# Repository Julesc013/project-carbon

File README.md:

# Project Carbon

A family of retro-style computer designs (hardware code, simulators, and schematics) built around shared specifications so different implementations stay compatible.

## Overview

Project Carbon is a repository for designing and testing classic-style computers: it includes hardware design files, code that describes CPUs and systems, and simulators that let you run small programs without building physical hardware.

What makes it distinct is its **contract-first** approach: the architecture is defined as machine-readable specifications, and the project generates shared constants and documentation from those specs so every core, system, and test agrees on the same rules.

This reduces the chance that cores, tests, docs, and tools quietly diverge over time.

What it is **not**:
- A complete, end-user computer kit or a polished emulator distribution.
- A repository of copyrighted ROMs or operating system images (you must supply your own).
- A cycle-accurate reproduction of legacy buses and full peripheral ecosystems (many peripherals and timing models are explicitly deferred).

## Keypoints

- Frozen v1.0 architecture contracts in `hdl/spec/*.yaml` with generated SystemVerilog/C constants.
- Compatibility tier ladders and a single mode-switching contract (`MODEUP`/`RETMD`).
- Shared HDL interfaces (fabric/CSR/IRQ/debug/accelerator) plus contract tests.
- SystemVerilog cores: Z85, Z90, Z380, Z480 (P7 subset) and Am9513/Am9514/Am9515.
- x86/x87 lineage is explicitly deferred in v1.0 (see `docs/DEFERRED.md`).
- Integrated system simulation tops and regression runner targeting Icarus Verilog.
- `carbon-sim` C++ simulator for CP/M 2.2 and RomWBW-style platforms (ROMs not included).
- KiCad hardware: a Carbon_Z80 project plus a KiCad 9 schematic skeleton generator.

## Architecture

### Layering (source-of-truth → generated → implementations)

- **Docs & contracts**
  - `docs/ARCHITECTURE_OVERVIEW.md`: human overview of the v1.0 contract freeze.
  - `hdl/spec/*.yaml`: machine-readable source of truth.
  - `hdl/tools/gen_specs.py` → generates `hdl/gen/*` and renders `docs/ARCH_CONTRACTS.md`.
- **HDL cores (CPU/accelerators)**
  - `hdl/cores/*`: CPU families and accelerators (RTL + testbenches + per-core docs).
- **HDL systems (integrations)**
  - `hdl/systems/*`: integrated "tops" (core + ROM/RAM + memory-mapped I/O + wiring) with smoke tests and memory maps.
- **HDL simulation & verification**
  - `hdl/sim/*`: Makefile-based smoke/contract/system tests (Icarus Verilog), driven by `hdl/sim/tests/regress.yaml`.
- **Host-level simulator(s)**
  - `source/sim/carbon_sim`: `carbon-sim` (C++17) with CP/M 2.2, RomWBW, and CarbonZ platform models; optional Verilator backend is scaffolding.
- **OS/software/firmware (repository content)**
  - `source/`: currently includes `carbon-sim`, a bundled Small Computer Workshop tool under `source/SCM/`, and placeholder directories (e.g., `source/JC-BIOS`, `source/JC-DOS`).
- **Schematics**
  - `schem/Carbon_Z80`: a KiCad project with exported PDFs/PNGs/SVGs under `schem/Carbon_Z80/export/`.
  - `schem/kicad9`: generator-owned schematic skeletons (`generated/`) plus hand-edited space (`manual/`) driven by mapping specs (`spec/`).

### Boot models (summary)

- **Carbon native boot**: ROM discovery → BDT/CAPSET → BIOS services → OS handoff.
- **Z80 boot** (RC2014/S-100 and similar): board pack or ROMWBW hooks; see `docs/boot_z80.md`.
- **PC BIOS boot**: PAL hooks with BIOS services; see `docs/boot_pcbios.md`.

### Design philosophy (as implemented in v1)

- **Determinism & reproducibility**: generators are deterministic; CI verifies generated outputs are committed.
- **Explicit contracts**: shared enums/bitfields/opcode pages/queue formats live in specs, not ad-hoc RTL.
- **Portability-minded tooling**: scripts exist for POSIX shell and PowerShell; generators avoid third-party dependencies.
- **Long-term maintainability**: clean module boundaries (notably the Z480 scaffold) so implementations can evolve behind stable interfaces.

## Platforms

Hardware targets (v1 focus):
- **Carbon native SoCs** (Z85/Z90/Z380/Z480 system tops).
- **Z80-class boards** via board packs (RC2014, S-100).
- **PC compatibles** via PAL BIOS hooks (UEFI PAL is a stub in v1).

Primary (actively used by the repo and CI):
- **HDL regression**: Icarus Verilog (`iverilog`/`vvp`) + `make` via `hdl/sim/`.
- **Spec/code generation**: Python via `scripts/gen_arch.*`.

Secondary / experimental:
- **`carbon-sim` desktop simulator**: CMake build (`source/sim/carbon_sim`); optional Verilator backend is preview scaffolding.
- **KiCad schematics**: Carbon_Z80 KiCad project and KiCad 9 generated skeletons under `schem/kicad9/generated/`.

Compatibility overview (guest focus):
- **CP/M** (2.x/3.x) and RomWBW-style guests are target environments.
- **DOS** real-mode guests are hosted via EE providers.
- **GEM** and **Windows** compatibility notes live in `docs/compat_gem.md` and `docs/compat_windows.md`.

## Audience

This project is for:
- RTL/hardware engineers exploring CPU, accelerator, and system integration patterns with explicit contracts.
- Retrocomputing hobbyists who want a testable platform (simulation + schematics) for “small computer” designs.
- Contributors who prefer deterministic generators and contract tests over hand-maintained duplicated constants.

Example use cases:
- Implement a new core or accelerator that conforms to the v1 contract layer.
- Run contract/system smoke tests to validate integration plumbing.
- Use `carbon-sim` to bring up ROM-based environments you supply (e.g., CP/M or RomWBW variants).

Not a fit if you need:
- Turn-key ROMs/OS images or full software distributions.
- Full instruction/peripheral coverage and cycle-accurate platform timing (see deferred lists and per-core docs).

## Constraints

- **Contracts are the source of truth**: `hdl/spec/*.yaml` drives generated headers/packages and the rendered contract reference.
- **Generated outputs are treated as artifacts**: `hdl/gen/*` and `docs/ARCH_CONTRACTS.md` are generated and committed (verified in CI).
- **Minimal dependency stance**: key tooling is dependency-light (e.g., a deterministic, stdlib-only spec generator; a simple regression manifest; JSON-in-YAML KiCad mapping specs).
- **Compatibility and gating are explicit**: tier ladders, `MODEUP`/`RETMD`, and strict-mode extension gating are architectural concepts, not local hacks.
- **Generated vs hand-edited separation**: `schem/kicad9/generated/` is safe to overwrite; `schem/kicad9/manual/` is not.

## Structure

- `docs/`: architecture/contracts docs plus legacy design notes, manuals, datasheets, and images.
- `hdl/`: HDL contract layer and implementations.
  - `hdl/spec/`: v1.0 specs (source of truth).
  - `hdl/gen/`: generated constants (committed; do not hand-edit).
  - `hdl/common/`: shared interfaces/utilities.
  - `hdl/cores/`: CPU/accelerator RTL + TBs.
  - `hdl/systems/`: integrated system tops + TBs.
  - `hdl/sim/`: regression harness and tests.
- `schem/`: KiCad projects and schematic generation.
  - `schem/Model_150/`: board-level KiCad project + exports.
  - `schem/kicad9/`: generated/manual schematic trees + mapping specs.
- `source/`: software and simulator sources (notably `source/sim/carbon_sim`).
- `scripts/`: wrappers for regenerating specs, running HDL regressions, and regenerating KiCad skeletons.
- `tools/`: utilities (`tools/kicadgen` and `tools/mk_disk.py`).

## Documentation

- Documentation index: `docs/README.md`
- Architecture overview and layering: `docs/ARCHITECTURE.md`
- Hardware architecture: `docs/HARDWARE_ARCHITECTURE.md`
- Firmware architecture: `docs/FIRMWARE_ARCHITECTURE.md`
- OS architecture: `docs/OS_ARCHITECTURE.md`
- PAL and EE contract indexes: `docs/PAL.md` and `docs/EE.md`
- Contracts, determinism, and style: `docs/CONTRACTS.md`, `docs/DEPENDENCIES.md`,
  `docs/DETERMINISM.md`, `docs/STYLE.md`
- Frozen contract reference (generated): `docs/ARCH_CONTRACTS.md`
- Spec entry points: `docs/SPEC_*.md`
- Compatibility ladders (CPU/FPU tiers): `docs/COMPAT_LADDERS.md`
- System memory map index: `docs/platform/SYSTEM_MEMORY_MAPS.md`
- CPU core docs:
  - `hdl/cores/Z85/docs/Z85_v1.md`
  - `hdl/cores/Z90/docs/Z90_v1.md`
  - `hdl/cores/Z380/docs/Z380.md`
  - `hdl/cores/Z480/docs/Z480.md`
- FPU tier docs:
  - `docs/fpu/Am9513.md`
  - `docs/fpu/Am9514.md`
  - `docs/fpu/Am9515.md`
- Verification flow and regression philosophy: `docs/VERIFICATION.md`
- HDL contract layer README: `hdl/README.md`
- v1.0 release contents: `docs/RELEASE_v1.md`
- Deferred/non-goals list (v1.0): `docs/DEFERRED.md`
- HDL simulation prerequisites/usage: `hdl/sim/README.md`
- System memory maps & smoke tests (examples):
  - `hdl/systems/CarbonZ80/docs/MEMORY_MAP.md`
  - `hdl/systems/CarbonX96/docs/MEMORY_MAP.md`
- `carbon-sim` usage and platform maps:
  - `source/sim/carbon_sim/docs/USAGE.md`
  - `source/sim/carbon_sim/docs/PLATFORMS.md`
  - ROM policy: `source/sim/carbon_sim/roms/README.md`
- KiCad 9 generated/manual workflow: `schem/kicad9/docs/USAGE.md`
- Carbon_Z80 schematic/PCB exports: `schem/Carbon_Z80/export/Carbon_Z80_150_sch_rev1.pdf`
- Release notes: `CHANGELOG.md`

## Build

- HDL (generate + run regressions): see `hdl/sim/README.md` and `docs/RELEASE_v1.md`.
- `carbon-sim` (build/run): see `source/sim/carbon_sim/docs/USAGE.md`.
- KiCad skeleton regeneration: see `schem/kicad9/docs/USAGE.md`.

## Status

- Repository version: **v1.0.0** (`VERSION`).
- The **contract/spec layer is frozen for v1.0** and the generator outputs are CI-checked for reproducibility.
- Several cores and systems are intentionally **subset implementations** (e.g., partial legacy ISA coverage, minimal peripherals); see `docs/DEFERRED.md` and the per-core docs under `hdl/cores/*/docs/`.
- x86/x87 lineage and CarbonX* system validation are deferred for v1.0.
- The primary “known-good” workflows in v1.0 are spec generation and HDL regression in CI; additional platforms (e.g., `carbon-sim` backends) evolve separately.

## License

License: just behave yourselves.

## Contributing

This repository includes CI and regression tooling under `.github/` and `scripts/`. If you contribute changes, keep generated outputs in sync and include enough context in your PR/commit to review the contract impact.

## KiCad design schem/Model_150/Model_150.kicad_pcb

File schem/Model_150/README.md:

Model: 150
Family: Carbon
Processor: Z80

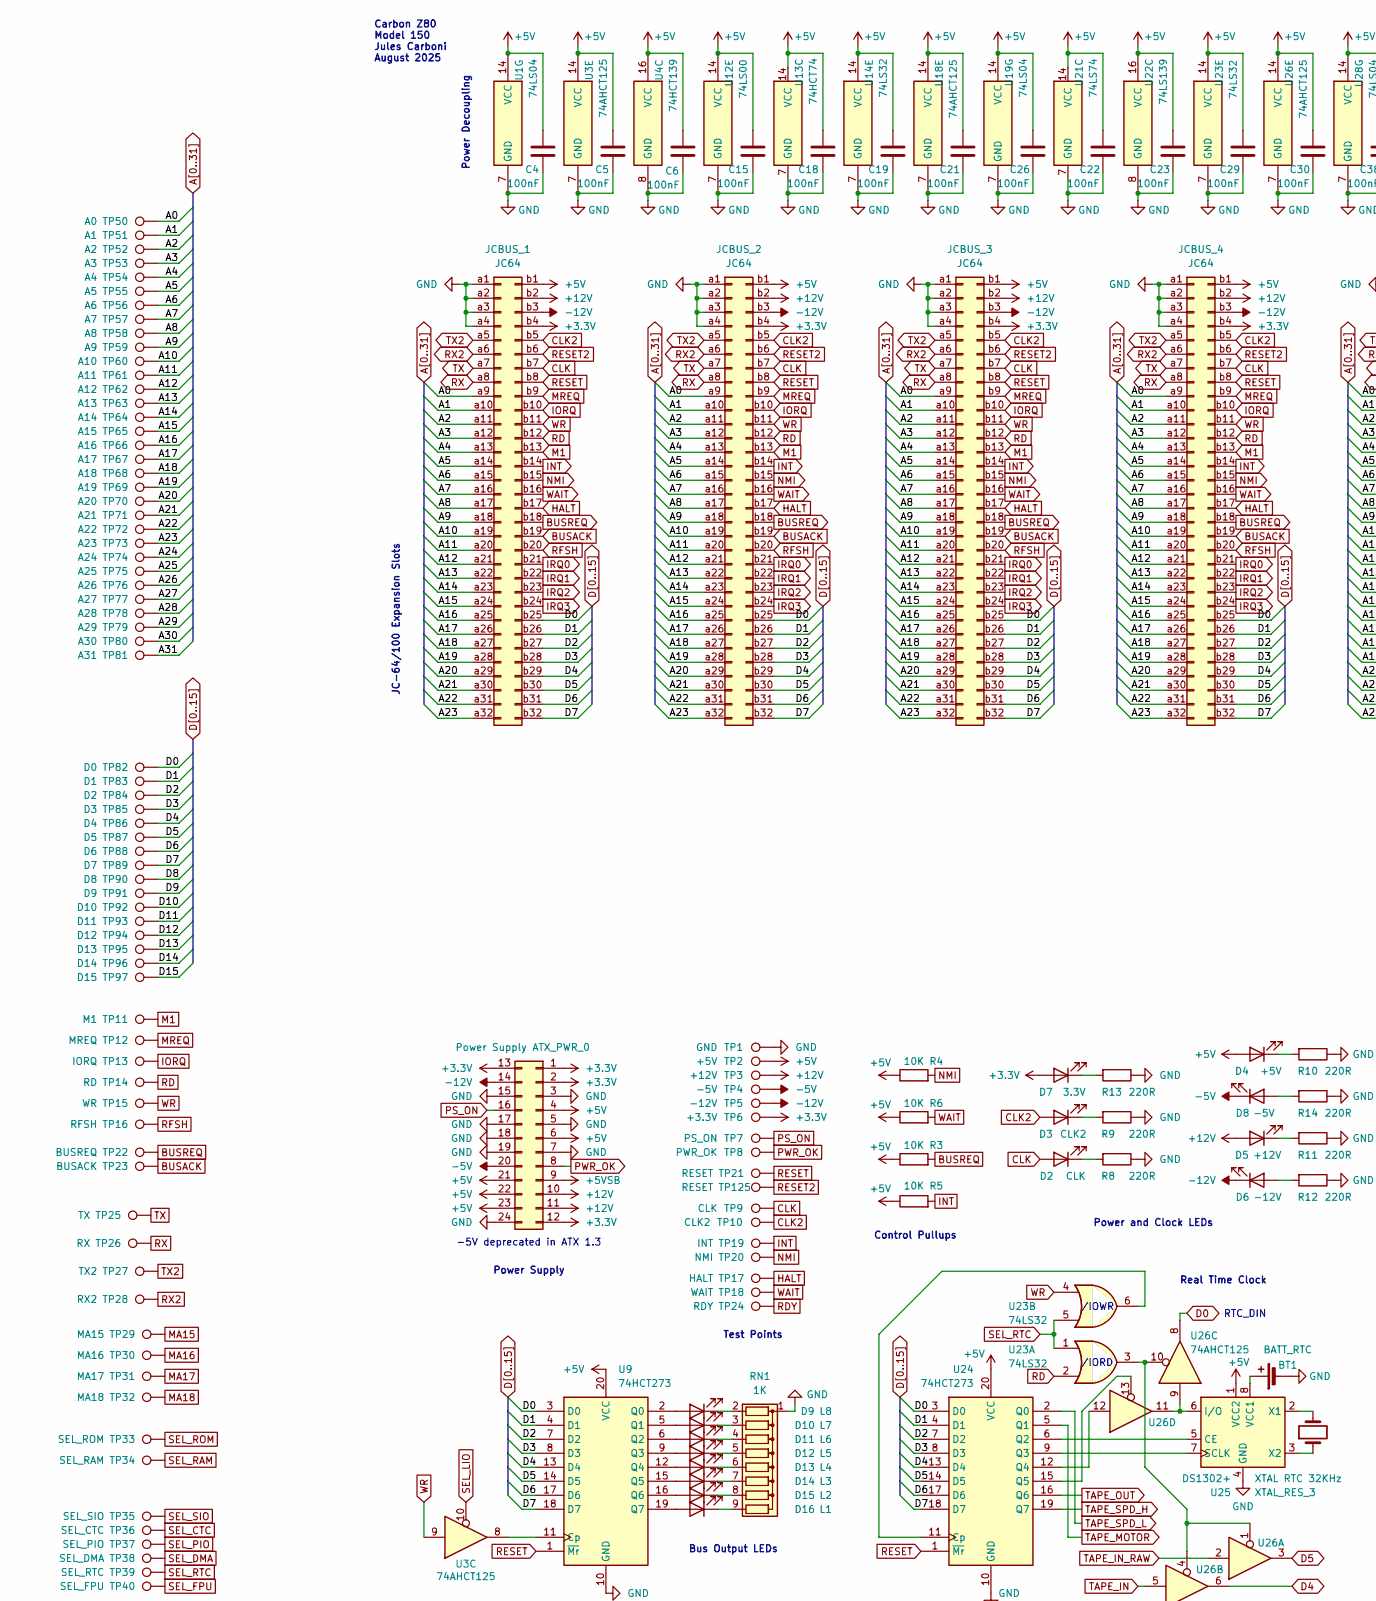
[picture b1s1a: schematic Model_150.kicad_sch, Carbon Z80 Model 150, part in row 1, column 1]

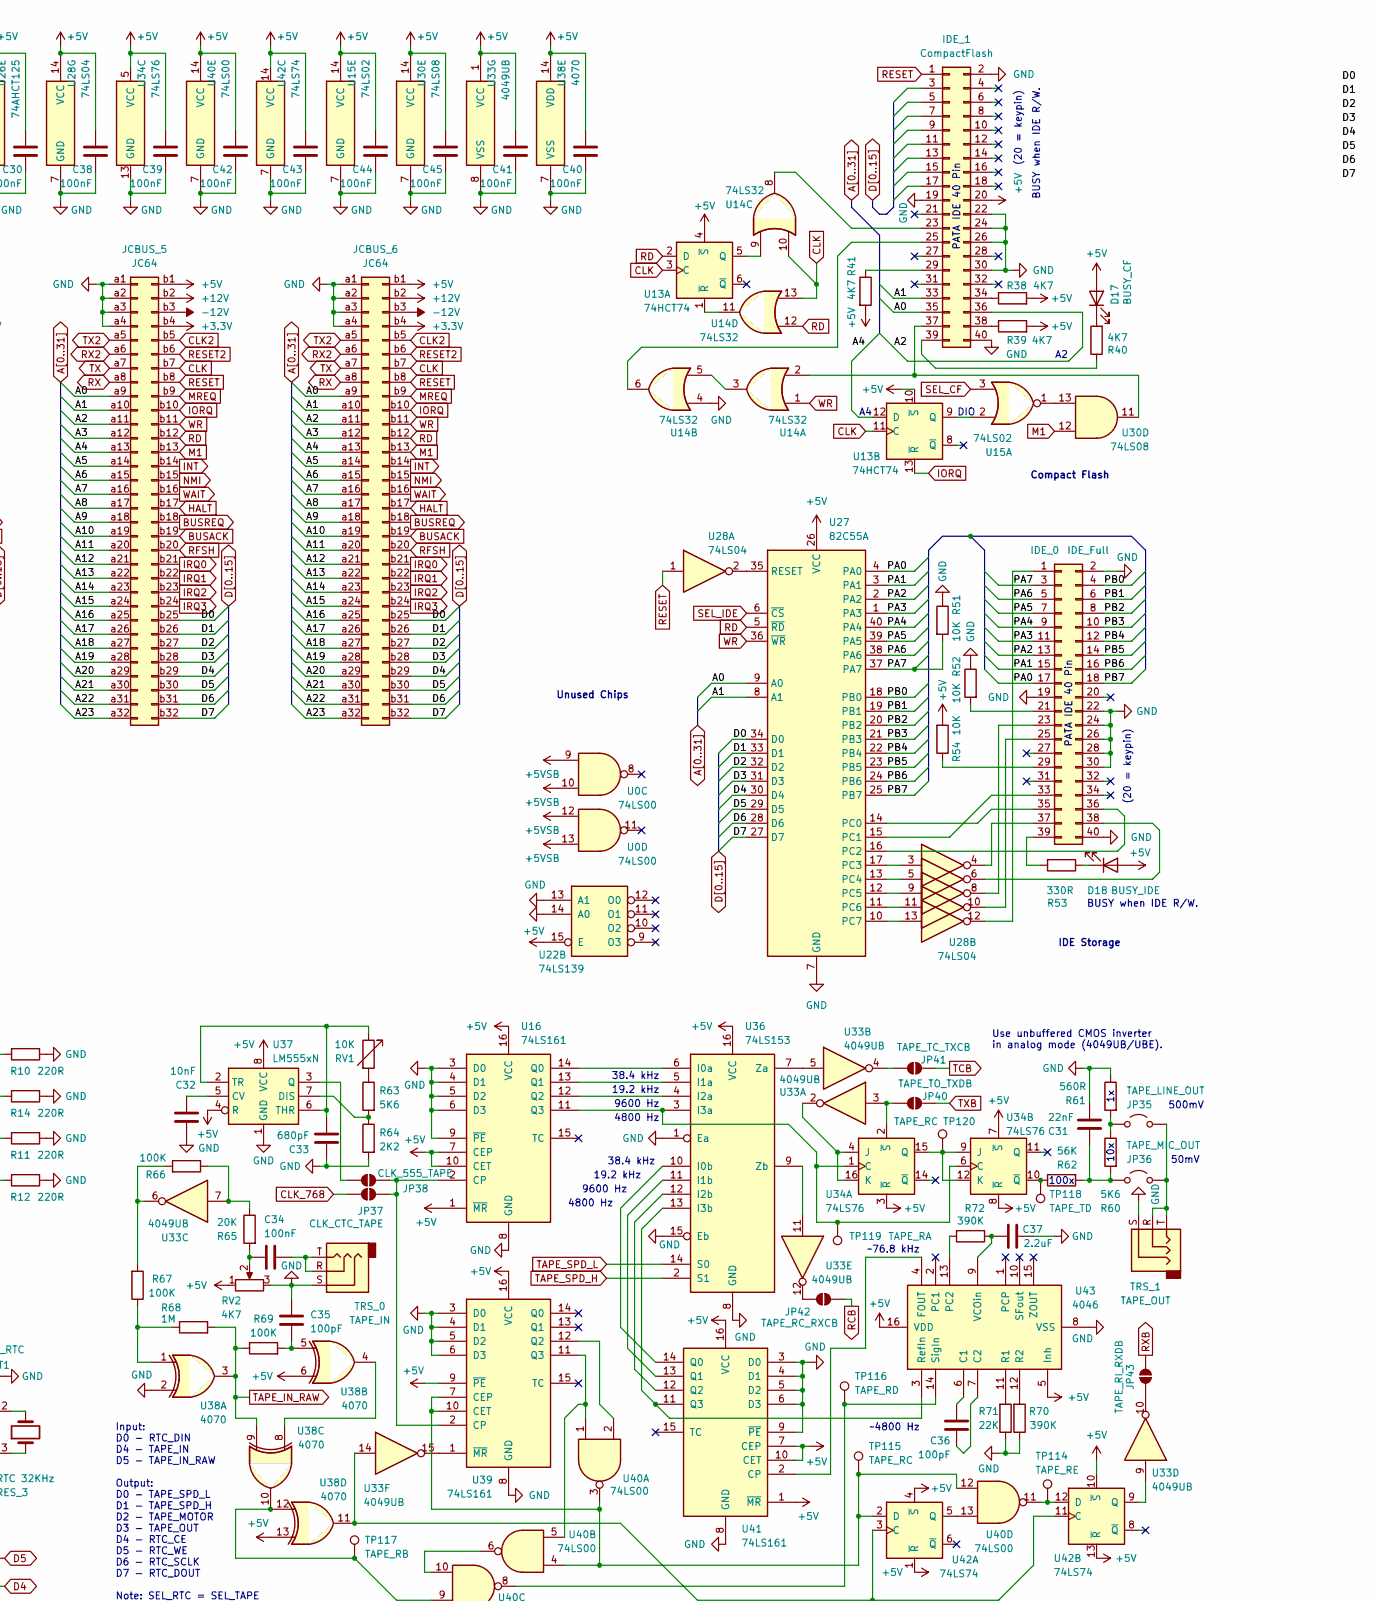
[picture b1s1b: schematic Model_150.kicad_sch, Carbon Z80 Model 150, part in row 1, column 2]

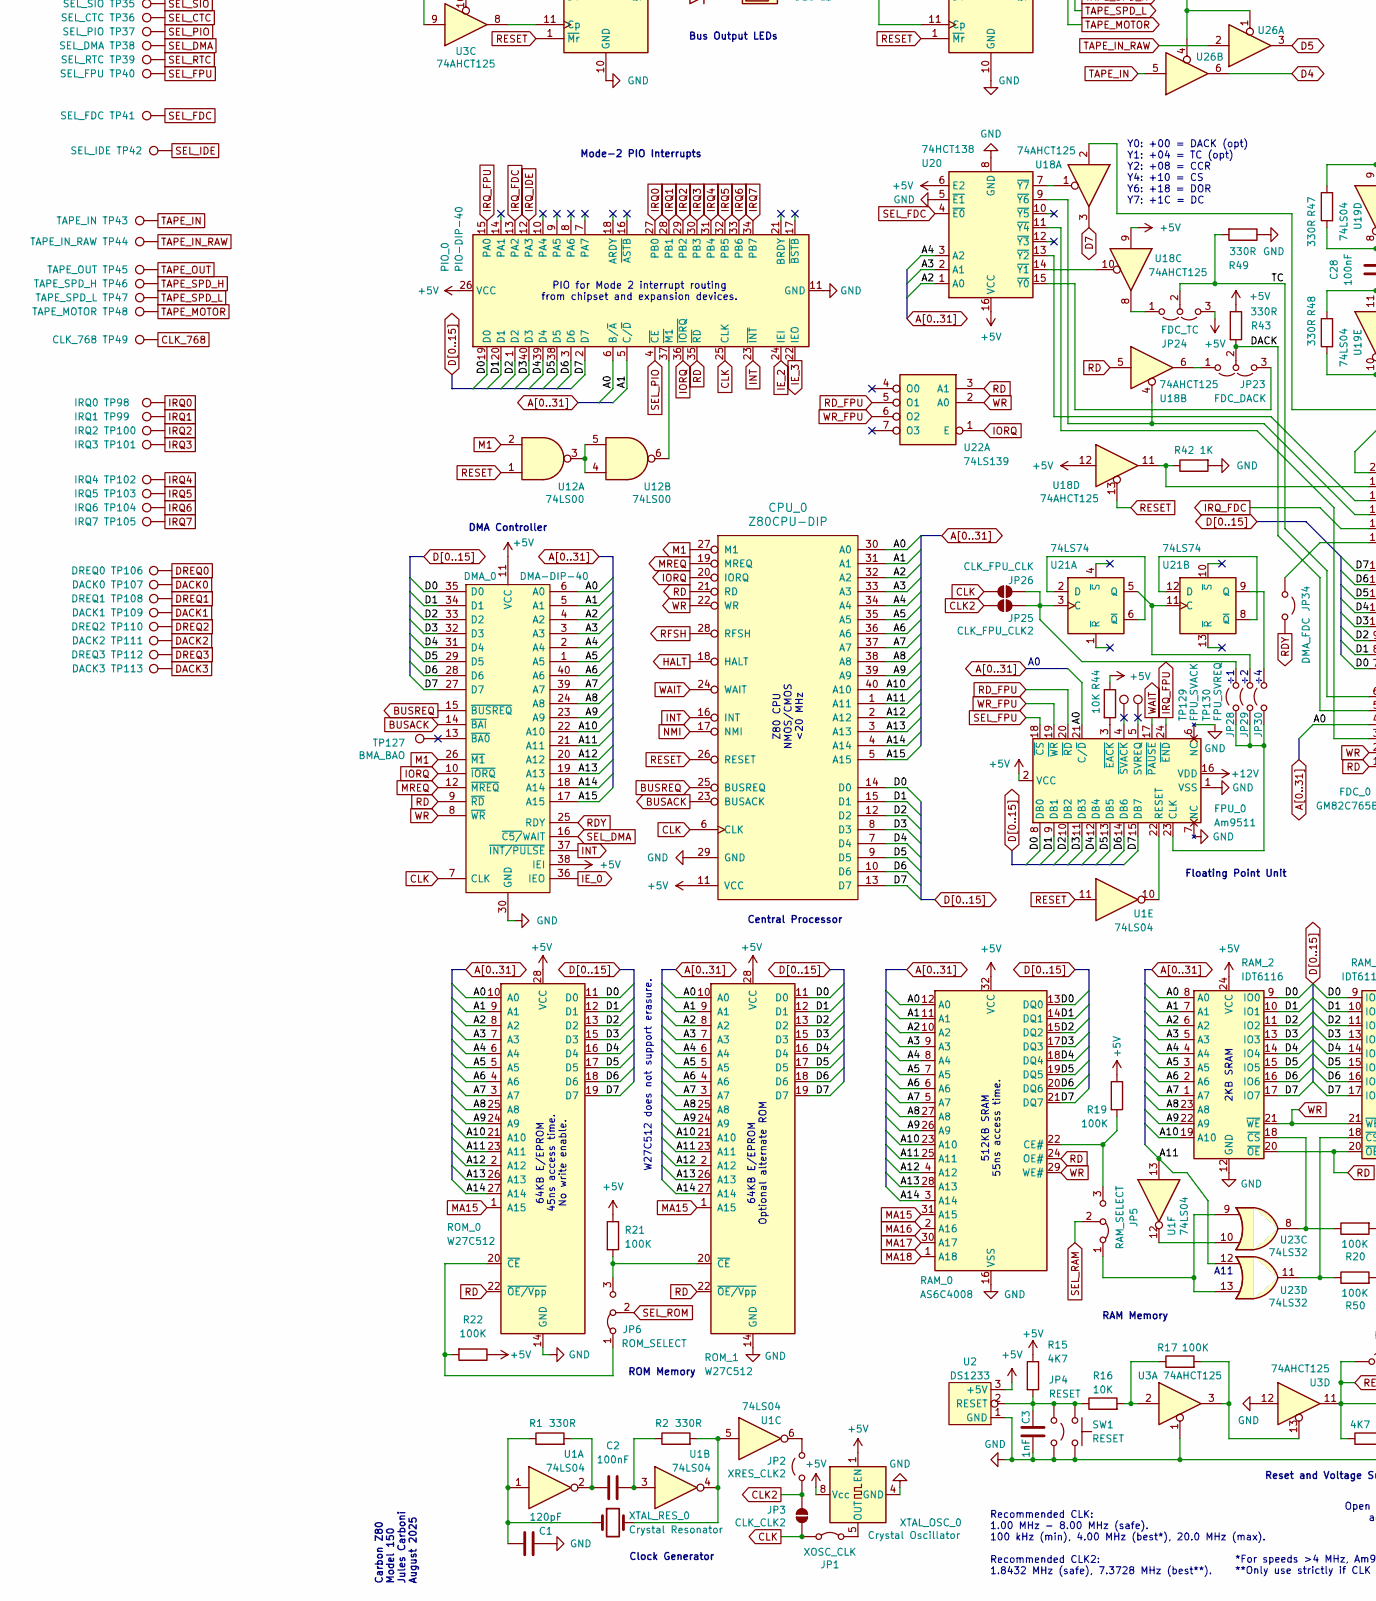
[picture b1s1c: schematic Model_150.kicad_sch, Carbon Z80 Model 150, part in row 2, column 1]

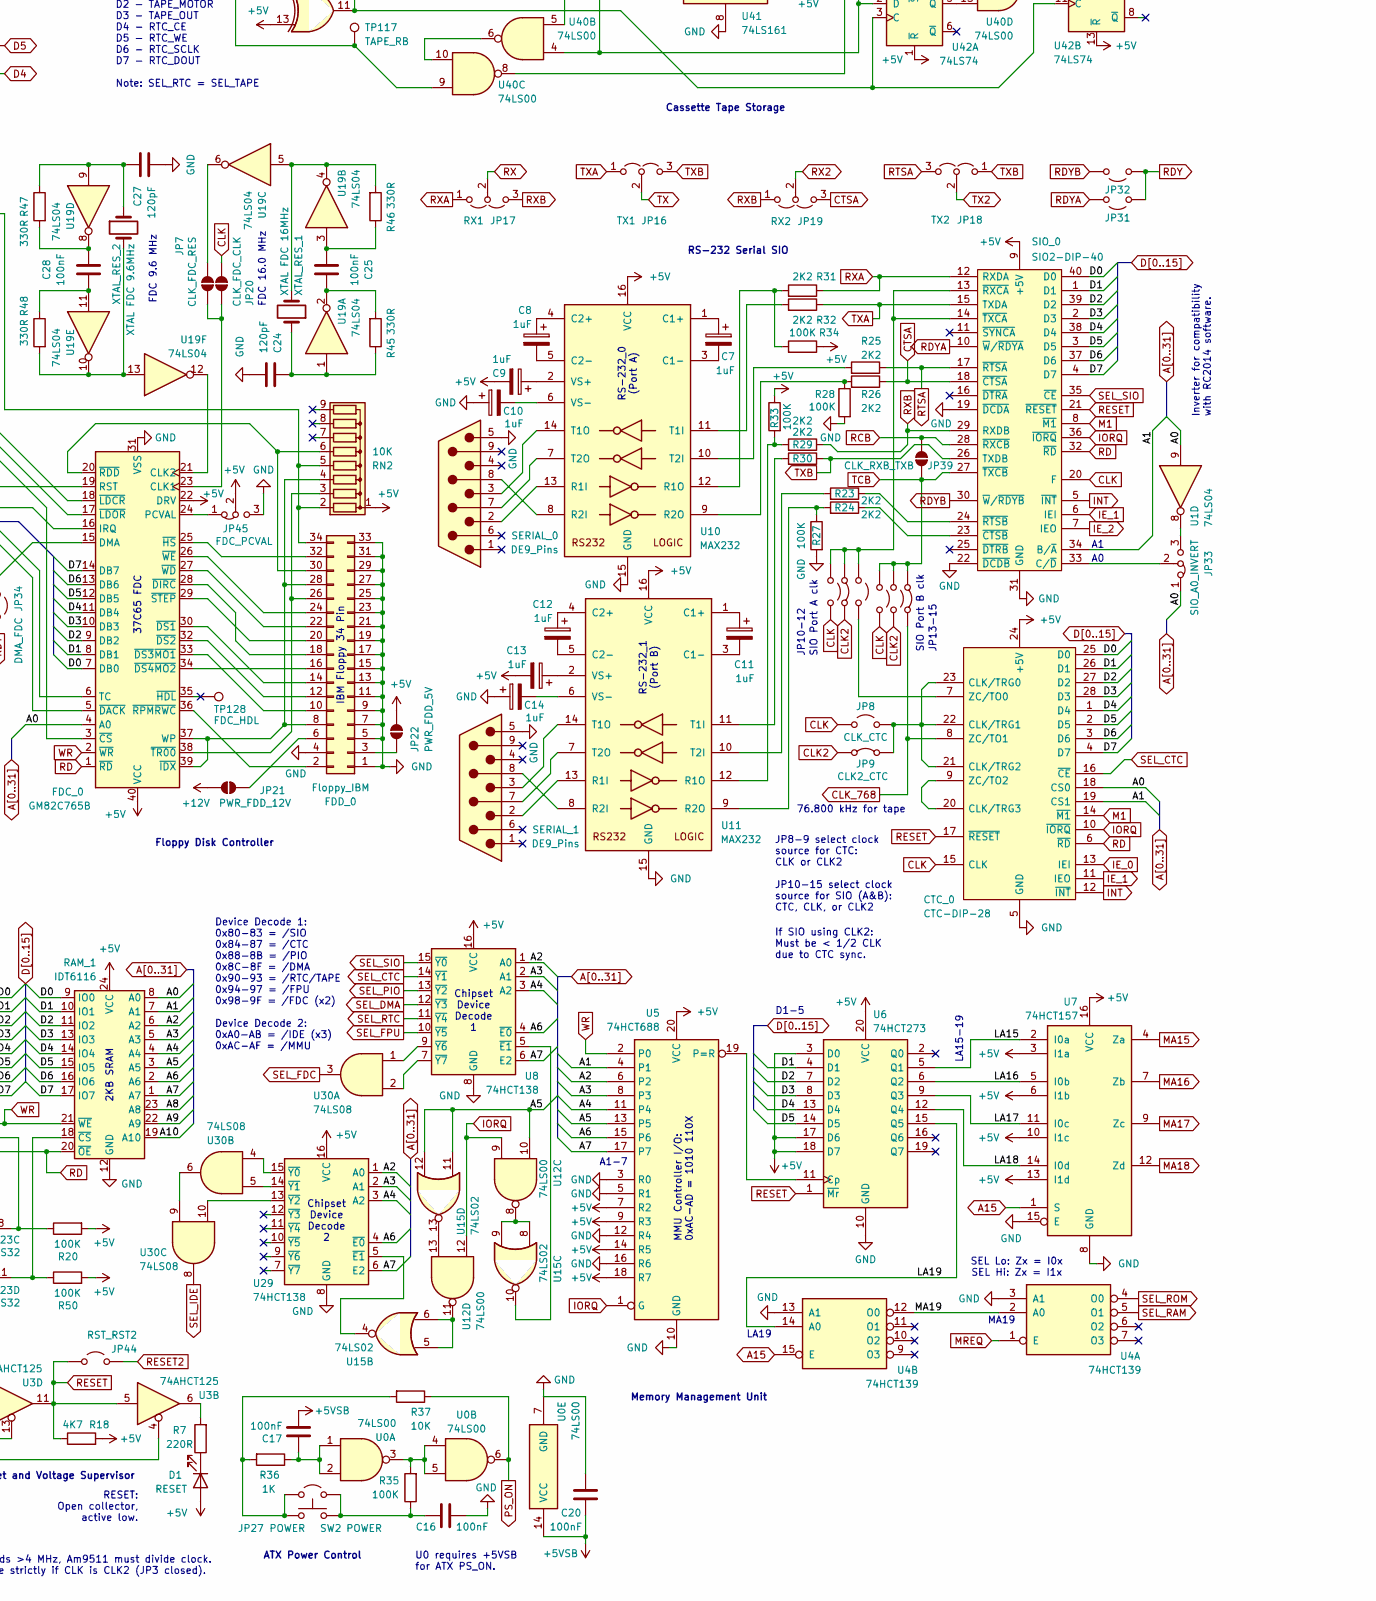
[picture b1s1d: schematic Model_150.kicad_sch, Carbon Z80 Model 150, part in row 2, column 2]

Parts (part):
ATX_PWR_0: Power Supply; Molex_Mini-Fit_Jr_5566-24A_2x12_P4.20mm_Vertical
BT1: BATT_RTC; BatteryHolder_MYOUNG_BS-07-A1BJ001_CR2032
C1, C24, C27: 120pF; C_Disc_D3.4mm_W2.1mm_P2.50mm
C2, C4, C5, C6, C15, C16, C17, C18, C19, C20, C21, C22, C23, C25, C26, C28, C29, C30, C34, C38, C39, C40, C41, C42, C43, C44, C45: 100nF; C_Disc_D5.0mm_W2.5mm_P2.50mm
C3: 1nF; C_Disc_D5.0mm_W2.5mm_P2.50mm
C7, C8, C9, C10, C11, C12, C13, C14: 1uF; CP_Radial_D4.0mm_P2.00mm
C31: 22nF; C_Rect_L7.0mm_W3.5mm_P5.00mm
C32: 10nF
C33: 680pF
C35, C36: 100pF; C_Disc_D3.4mm_W2.1mm_P2.50mm
C37: 2.2uF; C_Disc_D6.0mm_W2.5mm_P5.00mm
CPU_0: Z80CPU-DIP; DIP-40_W15.24mm_Socket
CTC_0: CTC-DIP-28; DIP-28_W15.24mm_LongPads; Manufacturer_Part_Number Z84C3010PEG; Mouser Part Number 692-Z84C3010PEG
D1: RESET; LED_D5.0mm
D2: CLK; LED_D5.0mm
D3: CLK2; LED_D5.0mm
D4: +5V; LED_D5.0mm
D5: +12V; LED_D5.0mm
D6: -12V; LED_D5.0mm
D7: 3.3V; LED_D5.0mm
D8: -5V; LED_D5.0mm
D9: L8; LED_D5.0mm
D10: L7; LED_D5.0mm
D11: L6; LED_D5.0mm
D12: L5; LED_D5.0mm
D13: L4; LED_D5.0mm
D14: L3; LED_D5.0mm
D15: L2; LED_D5.0mm
D16: L1; LED_D5.0mm
D17: BUSY_CF; LED_D5.0mm
D18: BUSY_IDE; LED_D5.0mm
DMA_0: DMA-DIP-40; DIP-40_W15.24mm_Socket; Manufacturer_Part_Number Z84C4206PEG; Mouser Part Number 692-Z84C4206PEG
FDC_0: GM82C765B; DIP-40_W15.24mm_Socket
FDD_0: Floppy_IBM; IDC-Header_2x17_P2.54mm_Vertical
FPU_0: Am9511; DIP-24_W15.24mm
IDE_0: IDE_Full; IDC-Header_2x20_P2.54mm_Vertical
IDE_1: CompactFlash; IDC-Header_2x20_P2.54mm_Vertical
JCBUS_1, JCBUS_2, JCBUS_3, JCBUS_4, JCBUS_5, JCBUS_6: JC64; JC64_Bus_8b
JP1: XOSC_CLK; PinHeader_1x02_P2.54mm_Vertical
JP2: XRES_CLK2; PinHeader_1x02_P2.54mm_Vertical
JP3: CLK_CLK2
JP4: RESET; PinHeader_1x02_P2.54mm_Vertical
JP5: RAM_SELECT; PinHeader_1x03_P2.54mm_Vertical
JP6: ROM_SELECT; PinHeader_1x03_P2.54mm_Vertical
JP7: CLK_FDC_RES
JP8: CLK_CTC; PinHeader_1x02_P2.54mm_Vertical
JP9: CLK2_CTC
JP10: CLK_SIOA; PinHeader_1x02_P2.54mm_Vertical
JP11: CLK2_SIOA
JP12: CTC_SIOA; PinHeader_1x02_P2.54mm_Vertical
JP13: CLK_SIOB; PinHeader_1x02_P2.54mm_Vertical
JP14: CLK2_SIOB; PinHeader_1x02_P2.54mm_Vertical
JP15: CTC_SIOB
JP16: TX1; PinHeader_1x03_P2.54mm_Vertical
JP17: RX1; PinHeader_1x03_P2.54mm_Vertical
JP18: TX2; PinHeader_1x03_P2.54mm_Vertical
JP19: RX2; PinHeader_1x03_P2.54mm_Vertical
JP20: CLK_FDC_CLK
JP21: PWR_FDD_12V
JP22: PWR_FDD_5V
JP23: FDC_DACK; PinHeader_1x03_P2.54mm_Vertical
JP24: FDC_TC; PinHeader_1x03_P2.54mm_Vertical
JP25: CLK_FPU_CLK2
JP26: CLK_FPU_CLK
JP27: POWER; PinHeader_1x02_P2.54mm_Vertical
JP28: FPU_CLKd1; PinHeader_1x02_P2.54mm_Vertical
JP29: FPU_CLKd2; PinHeader_1x02_P2.54mm_Vertical
JP30: FPU_CLKd4; PinHeader_1x02_P2.54mm_Vertical
JP31: DMA_RDYA; PinHeader_1x02_P2.54mm_Vertical
JP32: DMA_RDYB; PinHeader_1x02_P2.54mm_Vertical
JP33: SIO_A0_INVERT; PinHeader_1x03_P2.54mm_Vertical
JP34: DMA_FDC; PinHeader_1x02_P2.54mm_Vertical
JP35: TAPE_LINE_OUT
JP36: TAPE_MIC_OUT
JP37: CLK_CTC_TAPE
JP38: CLK_555_TAPE
JP39: CLK_RXB_TXB
JP40: TAPE_TO_TXDB
JP41: TAPE_TC_TXCB
JP42: TAPE_RC_RXCB
JP43: TAPE_RI_RXDB
JP44: RST_RST2; PinHeader_1x02_P2.54mm_Vertical
JP45: FDC_PCVAL; PinHeader_1x03_P2.54mm_Vertical
PIO_0: PIO-DIP-40; DIP-40_W15.24mm_Socket
R1, R2, R43, R45, R46, R47, R48, R49: 330R
R3, R4, R5, R6, R16, R37, R44, R52, R54: 10K; R_Axial_DIN0207_L6.3mm_D2.5mm_P10.16mm_Horizontal
R7, R8, R9, R10, R11, R12, R13, R14: 220R; R_Axial_DIN0207_L6.3mm_D2.5mm_P10.16mm_Horizontal
R15, R18, R38, R39, R40, R41: 4K7; R_Axial_DIN0207_L6.3mm_D2.5mm_P10.16mm_Horizontal
R17, R19, R20, R21, R22, R27, R28, R33, R34, R35, R50, R66, R67, R69: 100K; R_Axial_DIN0207_L6.3mm_D2.5mm_P10.16mm_Horizontal
R23, R24, R25, R26, R29, R30, R31, R32, R64: 2K2; R_Axial_DIN0207_L6.3mm_D2.5mm_P10.16mm_Horizontal
R36, R42: 1K; R_Axial_DIN0207_L6.3mm_D2.5mm_P10.16mm_Horizontal
R51: 10K
R53: 330R; R_Axial_DIN0207_L6.3mm_D2.5mm_P10.16mm_Horizontal
R60, R63: 5K6; R_Axial_DIN0207_L6.3mm_D2.5mm_P10.16mm_Horizontal
R61: 560R; R_Axial_DIN0207_L6.3mm_D2.5mm_P10.16mm_Horizontal
R62: 56K; R_Axial_DIN0207_L6.3mm_D2.5mm_P10.16mm_Horizontal
R65: 20K; R_Axial_DIN0207_L6.3mm_D2.5mm_P10.16mm_Horizontal
R68: 1M; R_Axial_DIN0207_L6.3mm_D2.5mm_P10.16mm_Horizontal
R70, R72: 390K; R_Axial_DIN0207_L6.3mm_D2.5mm_P10.16mm_Horizontal
R71: 22K; R_Axial_DIN0207_L6.3mm_D2.5mm_P10.16mm_Horizontal
RAM_0: AS6C4008; DIP-32_W15.24mm_Socket
RAM_1, RAM_2: IDT6116; DIP-24_W15.24mm_Socket
RN1: 1K; R_Array_SIP9
RN2: 10K; R_Array_SIP9
ROM_0, ROM_1: W27C512; DIP-28_W15.24mm_Socket
RV1: 10K
RV2: 4K7
SERIAL_0, SERIAL_1: DE9_Pins; DSUB-9_Pins_Horizontal_P2.77x2.84mm_EdgePinOffset7.70mm_Hou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
SIO_0: SIO2-DIP-40; DIP-40_W15.24mm_Socket; Manufacturer_Part_Number Z84C4206PEG; Mouser Part Number 692-Z84C4206PEG
SW1: RESET; SW_PUSH_6mm
SW2: POWER; SW_PUSH_6mm
TP1: GND; TestPoint_THTPad_1.5x1.5mm_Drill0.7mm
TP2: +5V; TestPoint_THTPad_1.5x1.5mm_Drill0.7mm
TP3: +12V; TestPoint_THTPad_1.5x1.5mm_Drill0.7mm
TP4: -5V; TestPoint_THTPad_1.5x1.5mm_Drill0.7mm
TP5: -12V; TestPoint_THTPad_1.5x1.5mm_Drill0.7mm
TP6: +3.3V; TestPoint_THTPad_1.5x1.5mm_Drill0.7mm
TP7: PS_ON; TestPoint_THTPad_1.5x1.5mm_Drill0.7mm
TP8: PWR_OK; TestPoint_THTPad_1.5x1.5mm_Drill0.7mm
TP9: CLK; TestPoint_THTPad_1.5x1.5mm_Drill0.7mm
TP10: CLK2; TestPoint_THTPad_1.5x1.5mm_Drill0.7mm
TP11: M1; TestPoint_THTPad_1.5x1.5mm_Drill0.7mm
TP12: MREQ; TestPoint_THTPad_1.5x1.5mm_Drill0.7mm
TP13: IORQ; TestPoint_THTPad_1.5x1.5mm_Drill0.7mm
TP14: RD; TestPoint_THTPad_1.5x1.5mm_Drill0.7mm
TP15: WR; TestPoint_THTPad_1.5x1.5mm_Drill0.7mm
TP16: RFSH; TestPoint_THTPad_1.5x1.5mm_Drill0.7mm
TP17: HALT; TestPoint_THTPad_1.5x1.5mm_Drill0.7mm
TP18: WAIT; TestPoint_THTPad_1.5x1.5mm_Drill0.7mm
TP19: INT; TestPoint_THTPad_1.5x1.5mm_Drill0.7mm
TP20: NMI; TestPoint_THTPad_1.5x1.5mm_Drill0.7mm
TP21, TP125: RESET; TestPoint_THTPad_1.5x1.5mm_Drill0.7mm
TP22: BUSREQ; TestPoint_THTPad_1.5x1.5mm_Drill0.7mm
TP23: BUSACK; TestPoint_THTPad_1.5x1.5mm_Drill0.7mm
TP24: RDY; TestPoint_THTPad_1.5x1.5mm_Drill0.7mm
TP25: TX; TestPoint_THTPad_1.5x1.5mm_Drill0.7mm
TP26: RX; TestPoint_THTPad_1.5x1.5mm_Drill0.7mm
TP27: TX2; TestPoint_THTPad_1.5x1.5mm_Drill0.7mm
TP28: RX2; TestPoint_THTPad_1.5x1.5mm_Drill0.7mm
TP29: MA15; TestPoint_THTPad_1.5x1.5mm_Drill0.7mm
TP30: MA16; TestPoint_THTPad_1.5x1.5mm_Drill0.7mm
TP31: MA17; TestPoint_THTPad_1.5x1.5mm_Drill0.7mm
TP32: MA18; TestPoint_THTPad_1.5x1.5mm_Drill0.7mm
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
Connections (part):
+3.3V: ATX_PWR_0.1, ATX_PWR_0.2, ATX_PWR_0.12, ATX_PWR_0.13, D7.2 (A), JCBUS_1.b4, JCBUS_2.b4, JCBUS_3.b4, JCBUS_4.b4, JCBUS_5.b4, JCBUS_6.b4, TP6.1 (1_1); also elsewhere on the board
+5V: ATX_PWR_0.4, ATX_PWR_0.6, ATX_PWR_0.21, ATX_PWR_0.22, ATX_PWR_0.23, C4.1, C5.1, C6.1, C9.2, C13.2, C15.1, C18.1, C19.1, C21.1, C22.1, C23.1, C26.1, C29.1, C30.1, C38.1, C39.1, C40.1, C41.1, C42.1, C43.1, C44.1, C45.1, CPU_0.11 (VCC), CTC_0.24 (+5V), D1.2 (A), D4.2 (A), D17.2 (A), D18.2 (A), DMA_0.11 (VCC), DMA_0.38 (IEI), FDC_0.22 (DRV), FDC_0.40 (VCC), FPU_0.2 (VCC), IDE_1.20, JCBUS_1.b1, JCBUS_2.b1, JCBUS_3.b1, JCBUS_4.b1, JCBUS_5.b1, JCBUS_6.b1, JP22.2 (B), JP24.3 (B), JP45.2 (C), PIO_0.26 (VCC), R3.1, R4.1, R5.1, R6.1, R15.1, R18.2, R19.1, R20.2, R21.1, R22.1, R33.1, R34.1, R38.2, R39.2, R41.2, R43.1, R44.1, R50.2, R54.2, RAM_0.32 (VCC), RAM_1.24 (VCC), RAM_2.24 (VCC), RN2.1 (common), ROM_0.28 (VCC), ROM_1.28 (VCC), RV2.1, SIO_0.9 (+5V), TP2.1 (1_1), U1.14 (VCC), U2.3 (+5V), U3.14 (VCC)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; also elsewhere on the board
+5VSB: ATX_PWR_0.9, C17.1, C20.2, U0.9, U0.10, U0.12, U0.13, U0.14 (VCC)
+12V: ATX_PWR_0.10, ATX_PWR_0.11, D5.2 (A), FPU_0.16 (VDD), JCBUS_1.b2, JCBUS_2.b2, JCBUS_3.b2, JCBUS_4.b2, JCBUS_5.b2, JCBUS_6.b2, JP21.2 (B), TP3.1 (1_1); also elsewhere on the board
-5V: ATX_PWR_0.20, D8.1 (K), TP4.1 (1_1)
-12V: ATX_PWR_0.14, D6.1 (K), JCBUS_1.b3, JCBUS_2.b3, JCBUS_3.b3, JCBUS_4.b3, JCBUS_5.b3, JCBUS_6.b3, TP5.1 (1_1); also elsewhere on the board
/DACK: FDC_0.5 (~DACK), JP23.2 (C), R43.2
/LA15: U6.5 (Q1), U7.2 (I0a)
/LA16: U6.6 (Q2), U7.5 (I0b)
/LA17: U6.9 (Q3), U7.11 (I0c)
/LA18: U6.12 (Q4), U7.14 (I0d)
/LA19: U4.14 (A0), U6.15 (Q5)
/MA19: U4.2 (A0), U4.12 (O0)
/PA0: IDE_0.17, U27.4 (PA0)
/PA1: IDE_0.15, U27.3 (PA1)
/PA2: IDE_0.13, U27.2 (PA2)
/PA3: IDE_0.11, U27.1 (PA3)
/PA4: IDE_0.9, U27.40 (PA4)
/PA5: IDE_0.7, U27.39 (PA5)
/PA6: IDE_0.5, U27.38 (PA6)
/PA7: IDE_0.3, R51.2, U27.37 (PA7)
/PB0: IDE_0.4, U27.18 (PB0)
/PB1: IDE_0.6, U27.19 (PB1)
/PB2: IDE_0.8, U27.20 (PB2)
/PB3: IDE_0.10, U27.21 (PB3)
/PB4: IDE_0.12, U27.22 (PB4)
/PB5: IDE_0.14, U27.23 (PB5)
/PB6: IDE_0.16, U27.24 (PB6)
/PB7: IDE_0.18, U27.25 (PB7)
/TC: FDC_0.6 (TC), JP24.2 (C), R49.2
A0: CPU_0.30 (A0), CTC_0.18 (CS0), DMA_0.6 (A0), FDC_0.4 (A0), FPU_0.21 (C/~D), IDE_1.35, JCBUS_1.a9, JCBUS_2.a9, JCBUS_3.a9, JCBUS_4.a9, JCBUS_5.a9, JCBUS_6.a9, JP33.1 (A), PIO_0.6 (B/~A), RAM_0.12 (A0), RAM_1.8 (A0), RAM_2.8 (A0), ROM_0.10 (A0), ROM_1.10 (A0), TP50.1 (1_1), U1.9, U27.9 (A0)
A1: CPU_0.31 (A1), CTC_0.19 (CS1), DMA_0.5 (A1), IDE_1.33, JCBUS_1.a10, JCBUS_2.a10, JCBUS_3.a10, JCBUS_4.a10, JCBUS_5.a10, JCBUS_6.a10, PIO_0.5 (C/~D), RAM_0.11 (A1), RAM_1.7 (A1), RAM_2.7 (A1), ROM_0.9 (A1), ROM_1.9 (A1), SIO_0.34 (B/~A), TP51.1 (1_1), U5.4 (P1), U27.8 (A1)
A2: CPU_0.32 (A2), DMA_0.4 (A2), IDE_1.36, JCBUS_1.a11, JCBUS_2.a11, JCBUS_3.a11, JCBUS_4.a11, JCBUS_5.a11, JCBUS_6.a11, RAM_0.10 (A2), RAM_1.6 (A2), RAM_2.6 (A2), ROM_0.8 (A2), ROM_1.8 (A2), TP52.1 (1_1), U5.6 (P2), U8.1 (A0), U20.1 (A0), U29.1 (A0)
A3: CPU_0.33 (A3), DMA_0.3 (A3), JCBUS_1.a12, JCBUS_2.a12, JCBUS_3.a12, JCBUS_4.a12, JCBUS_5.a12, JCBUS_6.a12, RAM_0.9 (A3), RAM_1.5 (A3), RAM_2.5 (A3), ROM_0.7 (A3), ROM_1.7 (A3), TP53.1 (1_1), U5.8 (P3), U8.2 (A1), U20.2 (A1), U29.2 (A1)
A4: CPU_0.34 (A4), DMA_0.2 (A4), JCBUS_1.a13, JCBUS_2.a13, JCBUS_3.a13, JCBUS_4.a13, JCBUS_5.a13, JCBUS_6.a13, RAM_0.8 (A4), RAM_1.4 (A4), RAM_2.4 (A4), ROM_0.6 (A4), ROM_1.6 (A4), TP54.1 (1_1), U5.11 (P4), U8.3 (A2), U13.12 (D), U20.3 (A2), U29.3 (A2)
A5: CPU_0.35 (A5), DMA_0.1 (A5), JCBUS_1.a14, JCBUS_2.a14, JCBUS_3.a14, JCBUS_4.a14, JCBUS_5.a14, JCBUS_6.a14, RAM_0.7 (A5), RAM_1.3 (A5), RAM_2.3 (A5), ROM_0.5 (A5), ROM_1.5 (A5), TP55.1 (1_1), U5.13 (P5), U12.10, U15.11, U15.12
A6: CPU_0.36 (A6), DMA_0.40 (A6), JCBUS_1.a15, JCBUS_2.a15, JCBUS_3.a15, JCBUS_4.a15, JCBUS_5.a15, JCBUS_6.a15, RAM_0.6 (A6), RAM_1.2 (A6), RAM_2.2 (A6), ROM_0.4 (A6), ROM_1.4 (A6), TP56.1 (1_1), U5.15 (P6), U8.4 (~E0), U29.4 (~E0)
A7: CPU_0.37 (A7), DMA_0.39 (A7), JCBUS_1.a16, JCBUS_2.a16, JCBUS_3.a16, JCBUS_4.a16, JCBUS_5.a16, JCBUS_6.a16, RAM_0.5 (A7), RAM_1.1 (A7), RAM_2.1 (A7), ROM_0.3 (A7), ROM_1.3 (A7), TP57.1 (1_1), U5.17 (P7), U8.6 (E2), U29.6 (E2)
A8: CPU_0.38 (A8), DMA_0.24 (A8), JCBUS_1.a17, JCBUS_2.a17, JCBUS_3.a17, JCBUS_4.a17, JCBUS_5.a17, JCBUS_6.a17, RAM_0.27 (A8), RAM_1.23 (A8), RAM_2.23 (A8), ROM_0.25 (A8), ROM_1.25 (A8), TP58.1 (1_1)
A9: CPU_0.39 (A9), DMA_0.23 (A9), JCBUS_1.a18, JCBUS_2.a18, JCBUS_3.a18, JCBUS_4.a18, JCBUS_5.a18, JCBUS_6.a18, RAM_0.26 (A9), RAM_1.22 (A9), RAM_2.22 (A9), ROM_0.24 (A9), ROM_1.24 (A9), TP59.1 (1_1)
A10: CPU_0.40 (A10), DMA_0.22 (A10), JCBUS_1.a19, JCBUS_2.a19, JCBUS_3.a19, JCBUS_4.a19, JCBUS_5.a19, JCBUS_6.a19, RAM_0.23 (A10), RAM_1.19 (A10), RAM_2.19 (A10), ROM_0.21 (A10), ROM_1.21 (A10), TP60.1 (1_1)
A11: CPU_0.1 (A11), DMA_0.21 (A11), JCBUS_1.a20, JCBUS_2.a20, JCBUS_3.a20, JCBUS_4.a20, JCBUS_5.a20, JCBUS_6.a20, RAM_0.25 (A11), ROM_0.23 (A11), ROM_1.23 (A11), TP61.1 (1_1), U1.13, U23.12
A12: CPU_0.2 (A12), DMA_0.20 (A12), JCBUS_1.a21, JCBUS_2.a21, JCBUS_3.a21, JCBUS_4.a21, JCBUS_5.a21, JCBUS_6.a21, RAM_0.4 (A12), ROM_0.2 (A12), ROM_1.2 (A12), TP62.1 (1_1)
A13: CPU_0.3 (A13), DMA_0.19 (A13), JCBUS_1.a22, JCBUS_2.a22, JCBUS_3.a22, JCBUS_4.a22, JCBUS_5.a22, JCBUS_6.a22, RAM_0.28 (A13), ROM_0.26 (A13), ROM_1.26 (A13), TP63.1 (1_1)
A14: CPU_0.4 (A14), DMA_0.18 (A14), JCBUS_1.a23, JCBUS_2.a23, JCBUS_3.a23, JCBUS_4.a23, JCBUS_5.a23, JCBUS_6.a23, RAM_0.3 (A14), ROM_0.27 (A14), ROM_1.27 (A14), TP64.1 (1_1)
A15: CPU_0.5 (A15), DMA_0.17 (A15), JCBUS_1.a24, JCBUS_2.a24, JCBUS_3.a24, JCBUS_4.a24, JCBUS_5.a24, JCBUS_6.a24, TP65.1 (1_1), U4.15 (E), U7.1 (S)
A16: JCBUS_1.a25, JCBUS_2.a25, JCBUS_3.a25, JCBUS_4.a25, JCBUS_5.a25, JCBUS_6.a25, TP66.1 (1_1)
A17: JCBUS_1.a26, JCBUS_2.a26, JCBUS_3.a26, JCBUS_4.a26, JCBUS_5.a26, JCBUS_6.a26, TP67.1 (1_1)
A18: JCBUS_1.a27, JCBUS_2.a27, JCBUS_3.a27, JCBUS_4.a27, JCBUS_5.a27, JCBUS_6.a27, TP68.1 (1_1)
A19: JCBUS_1.a28, JCBUS_2.a28, JCBUS_3.a28, JCBUS_4.a28, JCBUS_5.a28, JCBUS_6.a28, TP69.1 (1_1)
A20: JCBUS_1.a29, JCBUS_2.a29, JCBUS_3.a29, JCBUS_4.a29, JCBUS_5.a29, JCBUS_6.a29, TP70.1 (1_1)
A21: JCBUS_1.a30, JCBUS_2.a30, JCBUS_3.a30, JCBUS_4.a30, JCBUS_5.a30, JCBUS_6.a30, TP71.1 (1_1)
A22: JCBUS_1.a31, JCBUS_2.a31, JCBUS_3.a31, JCBUS_4.a31, JCBUS_5.a31, JCBUS_6.a31, TP72.1 (1_1)
A23: JCBUS_1.a32, JCBUS_2.a32, JCBUS_3.a32, JCBUS_4.a32, JCBUS_5.a32, JCBUS_6.a32, TP73.1 (1_1)
A24: TP74.1 (1_1)
A25: TP75.1 (1_1)
A26: TP76.1 (1_1)
A27: TP77.1 (1_1)
A28: TP78.1 (1_1)
A29: TP79.1 (1_1)
A30: TP80.1 (1_1)
A31: TP81.1 (1_1)
BUSACK: CPU_0.23 (BUSACK), DMA_0.14 (~BAI), JCBUS_1.b19, JCBUS_2.b19, JCBUS_3.b19, JCBUS_4.b19, JCBUS_5.b19, JCBUS_6.b19, TP23.1 (1_1); also elsewhere on the board
BUSREQ: CPU_0.25 (BUSREQ), DMA_0.15 (~BUSREQ), JCBUS_1.b18, JCBUS_2.b18, JCBUS_3.b18, JCBUS_4.b18, JCBUS_5.b18, JCBUS_6.b18, R3.2, TP22.1 (1_1); also elsewhere on the board
CLK: CPU_0.6 (CLK), CTC_0.15 (CLK), D2.2 (A), DMA_0.7 (CLK), JCBUS_1.b7, JCBUS_2.b7, JCBUS_3.b7, JCBUS_4.b7, JCBUS_5.b7, JCBUS_6.b7, JP1.2 (B), JP3.2 (B), JP8.2 (B), JP10.1 (A), JP13.1 (A), JP20.1 (A), JP26.2 (B), PIO_0.25 (CLK), SIO_0.20 (F), TP9.1 (1_1), U13.3 (C), U13.11 (C), U14.10, U14.13; also elsewhere on the board
CLK2: D3.2 (A), JCBUS_1.b5, JCBUS_2.b5, JCBUS_3.b5, JCBUS_4.b5, JCBUS_5.b5, JCBUS_6.b5, JP2.1 (A), JP3.1 (A), JP9.2 (B), JP11.1 (A), JP14.1 (A), JP25.2 (B), TP10.1 (1_1); also elsewhere on the board
CLK_768: CTC_0.8 (ZC/TO1), JP15.1 (A), JP37.2 (B), TP49.1 (1_1)
CTSA: JP19.3 (B), R26.1, SIO_0.18 (~CTSA)
D0: CPU_0.14 (D0), CTC_0.25 (D0), DMA_0.35 (D0), FDC_0.7 (DB0), FPU_0.8 (DB0), JCBUS_1.b25, JCBUS_2.b25, JCBUS_3.b25, JCBUS_4.b25, JCBUS_5.b25, JCBUS_6.b25, PIO_0.19 (D0), RAM_0.13 (DQ0), RAM_1.9 (IO0), RAM_2.9 (IO0), ROM_0.11 (D0), ROM_1.11 (D0), SIO_0.40 (D0), TP82.1 (1_1), U9.3 (D0), U24.3 (D0), U26.8, U27.34 (D0)
D1: CPU_0.15 (D1), CTC_0.26 (D1), DMA_0.34 (D1), FDC_0.8 (DB1), FPU_0.9 (DB1), JCBUS_1.b26, JCBUS_2.b26, JCBUS_3.b26, JCBUS_4.b26, JCBUS_5.b26, JCBUS_6.b26, PIO_0.20 (D1), RAM_0.14 (DQ1), RAM_1.10 (IO1), RAM_2.10 (IO1), ROM_0.12 (D1), ROM_1.12 (D1), SIO_0.1 (D1), TP83.1 (1_1), U6.4 (D1), U9.4 (D1), U24.4 (D1), U27.33 (D1)
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
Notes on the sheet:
38.4 kHz
SIO Port B clk
*For speeds >4 MHz, Am9511 must divide clock. **Only use strictly if CLK is CLK2 (JP3 closed).
9600 Hz
FDC 16.0 MHz
Test Points
JP13-15
Chipset Device Decode 1
JP8-9 select clock source for CTC: CLK or CLK2 JP10-15 select clock source for SIO (A&B): CTC, CLK, or CLK2
SEL Lo: Zx = I0x SEL Hi: Zx = I1x
RESET: Open collector, active low.
Bus Output LEDs
50mV
100x
Compact Flash
37C65 FDC
Power Supply
Power and Clock LEDs
Memory Management Unit
ROM Memory
500mV
PIO for Mode 2 interrupt routing from chipset and expansion devices.
Mode-2 PIO Interrupts
Z80 CPU NMOS/CMOS <20 MHz
RS-232_0 (Port A)
Recommended CLK: 1.00 MHz - 8.00 MHz (safe). 100 kHz (min), 4.00 MHz (best*), 20.0 MHz (max). Recommended CLK2: 1.8432 MHz (safe), 7.3728 MHz (best**).
JP10-12
D1-5
4800 Hz
Central Processor
Y0: +00 = DACK (opt) Y1: +04 = TC (opt) Y2: +08 = CCR Y4: +10 = CS Y6: +18 = DOR Y7: +1C = DC
Use unbuffered CMOS inverter in analog mode (4049UB/UBE).
64KB E/EPROM 45ns access time. No write enable.
Floating Point Unit
Cassette Tape Storage
PATA IDE 40 Pin
Carbon Z80 Model 150 Jules Carboni August 2025
MMU Controller I/O: 0xAC-AD = 1010 110X
W27C512 does not support erasure.
19.2 kHz

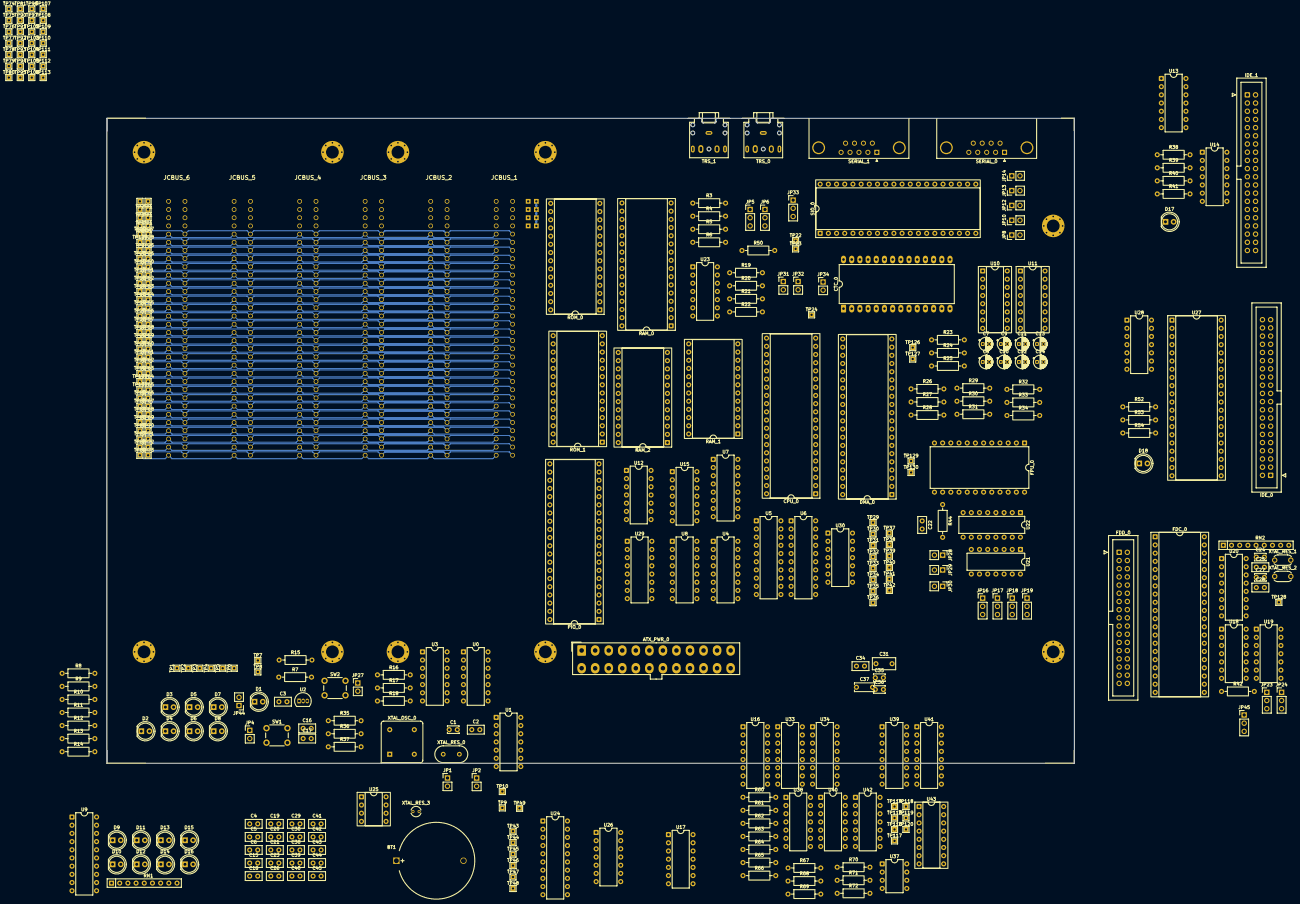
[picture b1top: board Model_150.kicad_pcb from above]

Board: 2 copper layers, 300.0 x 200.0 mm, 359 parts (0 on the bottom side), 347 nets.

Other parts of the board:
TP1#2, TP1#3, TP1#4, TP1#5: GND; TestPoint_THTPad_1.5x1.5mm_Drill0.7mm
TP2#2: +5V; TestPoint_THTPad_1.5x1.5mm_Drill0.7mm
TP3#2: +12V; TestPoint_THTPad_1.5x1.5mm_Drill0.7mm
TP5#2: -12V; TestPoint_THTPad_1.5x1.5mm_Drill0.7mm
TP6#2: +3.3V; TestPoint_THTPad_1.5x1.5mm_Drill0.7mm
TP9#2: CLK; TestPoint_THTPad_1.5x1.5mm_Drill0.7mm
TP10#2: CLK2; TestPoint_THTPad_1.5x1.5mm_Drill0.7mm
TP22#2: BUSREQ; TestPoint_THTPad_1.5x1.5mm_Drill0.7mm
TP23#2: BUSACK; TestPoint_THTPad_1.5x1.5mm_Drill0.7mm
TP126: DMA_BAI; TestPoint_THTPad_1.5x1.5mm_Drill0.7mm
U17: 74LS00; DIP-14_W7.62mm

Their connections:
+3.3V: TP6#2.1 (1_1); also elsewhere on the board
+5V: TP2#2.1 (1_1); also elsewhere on the board
+12V: TP3#2.1 (1_1); also elsewhere on the board
-12V: TP5#2.1 (1_1); also elsewhere on the board
BUSACK: TP23#2.1 (1_1); also elsewhere on the board
BUSREQ: TP22#2.1 (1_1); also elsewhere on the board
CLK: TP9#2.1 (1_1); also elsewhere on the board
CLK2: TP10#2.1 (1_1); also elsewhere on the board
GND: TP1#2.1 (1_1), TP1#3.1 (1_1), TP1#4.1 (1_1), TP1#5.1 (1_1); also elsewhere on the board
